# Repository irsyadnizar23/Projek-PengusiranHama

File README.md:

# Projek-Sistem Pengusiran hama otomatis berbasis mikrokontroler AVR 

Serangan hama dapat menyebabkan kerusakan yang signifikan pada tanaman dan menurunkan produktivitas. Untuk mengatasi masalah ini, saya mencoba mengembangkan sebuah sistem pengusiran hama otomatis berbasis mikrokontroler AVR. Sistem ini dirancang untuk mendeteksi keberadaan hama secara otomatis dan mengusir hama tersebut dengan metode yang efektif dan ramah lingkungan

---
Anggota
1. Rizal Fadhillah Muhammad (2122500032)
2. Samuel Windez Ambarita (2122500036)
3. Muhammad Irsyad Nizar Fazari (2122500050)
4. Nyoman Darma Saputra (2122500053)
5. Nashry Haliim Risantosa (2122500054)
---
## Komponen / alat yang diperlukan

1. Arduino Uno

   Mikrokontroler AVR bertindak sebagai otak dari sistem ini. Mikrokontroler akan menerima input dari sensor hama dan memproses data tersebut jika terdeteksi adanya       aktivitas hama

2. Led 3mm

   Sebagai indikator kepada para petani ketika hama datang menyerang 

3. Speaker

   Sebagai output suara dari hasil rekaman suara audacity kita  yang dapat didengar ketika kita menekan push button  

4. push Button(2)

   Push button kita menggunakan 2 push button yang push button pertama digunakan sebagai tombol untuk mengeluarkan suara hewan binatang buas dan push button kedua          digunakan sebagai suara ultrasonik dengan frekuensi tinggi 

5. Sensor sw 420

   sensor getaran yang digunakan untukMendeteksi keberadaan hama yang masuk di area pertanian dan mengirimkan sinyal ke mikrokontroler

6. PAM 8403

   Digunakan untuk menghasilkan output suara yang cukup keras dengan konsumsi daya yang rendah.

7. Pin Header male dan female

   sebagai soket tempat menghubungkan kabel-kabel konektor 

8. resistor 1k
9. Tip31c

---
## Skematik projek
Schematik

Board

Bottom

Top

LInk (https://youtu.be/SObbZaz81MM)
---
## Blog diagram

Cara Kerja

1. Saat ada Tikus atau Burung Pipit yang melewati atau menyentuh Padi Akan Membuat Padi Bergerak/bergetar
2. Getaran Dari Padi akan Di Deteksi Oleh Sensor Getar dan menghasilkan Sinyal Yang akan di kirim ke Mikrokontroler
3. Setelah Sinyal dari Sensor getar Di Terima oleh Mikrokontroler Maka Akan Membuat Led Menyala 
4. Dimana Disini LED sebagai Indikator terdapat Keberadaan Hama, Dimana Petani Dapat Menekan tombol (Button) seusai LED menyala yang akan Mengaktifkan Suara Pengusir Hama
5. Suara Output dari Mikrokontroler akan Di kuatkan Oleh Amplifier (penguat), Yang mana Suara Akan di keluarkan pada Speaker 
6. lalu Suara Yang akan di Keluarkan adalah Suara Hewan Buas contohnya Harimau, yang mana akan mengusir Tikus Dan Burung Pipit dari Tumbuhan Padi
---
## Simulasi projek
Disini kita coba mensimulasikan dengan menggunakan aplikasi wokwi

![Simulasi di wokwi] (https://wokwi.com/projects/398310246027706369)

LINK (https://youtu.be/nzQVdEaNT4E?si=r3UM6CYokPurmcue)
---
## Gambar Desain 3D
Tampak depan

Tampak samping

Dengan Dimensi

Tampak dalam

Hasil akhir 

Link Youtube
(https://youtu.be/AhoeIHWYmVM?si=7fZwOTttmSZrGxfX)

![Uploading 3d Desain] https://github.com/irsyadnizar23/Projek-PengusiranHama/blob/main/Desain%203D/File/alat%20pengusir%20hama%20new%20(1).blend

## Hasil cetak PCB

## Sistem audio
Disini untuk pembuatan audio kita menggunakan software audacity dan HXD yang kita gunakan untuk merekam hasil suara rekaman kita atau suara yang telah kita download bebrbentuk mp3
Berikut langkah langkah mengkonversi audio dari audacity hingga menjadi bahasa C:

   1. Buka aplikasi audacity
   2. Rekam suara atau dapat ambil audio dari web
   3. Setelah melakukan perekaman audio akan menghasilkan seperti dibawah ini

   4. Setelah diset noise nya agar pada audio tidak terdapat sebuah noise

   5. Export audio ke bentuk RAW

   6. Buka aplikasi HXD
   7. Klik open lalu pilih file RAW yang telah kita ekspor dari audacity

   8. lalu klik file lalu pilih export ke C, selanjutnya buka vs code pilih file yang telah kita export dari HXD

  LINK AUDACITY
  https://youtu.be/fRlAp86dA1M?si=hetPyFKCUFnrN079
  
## Dokumentasi Proses pengerjaan 
1. Mencoba sistem pada wokwi

2. Membuat desain 3d

3. Membuat shematik dan Board pada software eagle

4. pembelian komponen komponen yang diperlukan

5. Mensolder komponen pada PCB

6. Pembentukan casing menggunakan bor

7. Membuat rekaman audio pada audacity dan HXD

8. Membuat program pada arduino menggunakan arduino ide

9. Pengujian alat

Link simulasi 

(https://youtu.be/wmhCAvP-0ZI)

## Flyer

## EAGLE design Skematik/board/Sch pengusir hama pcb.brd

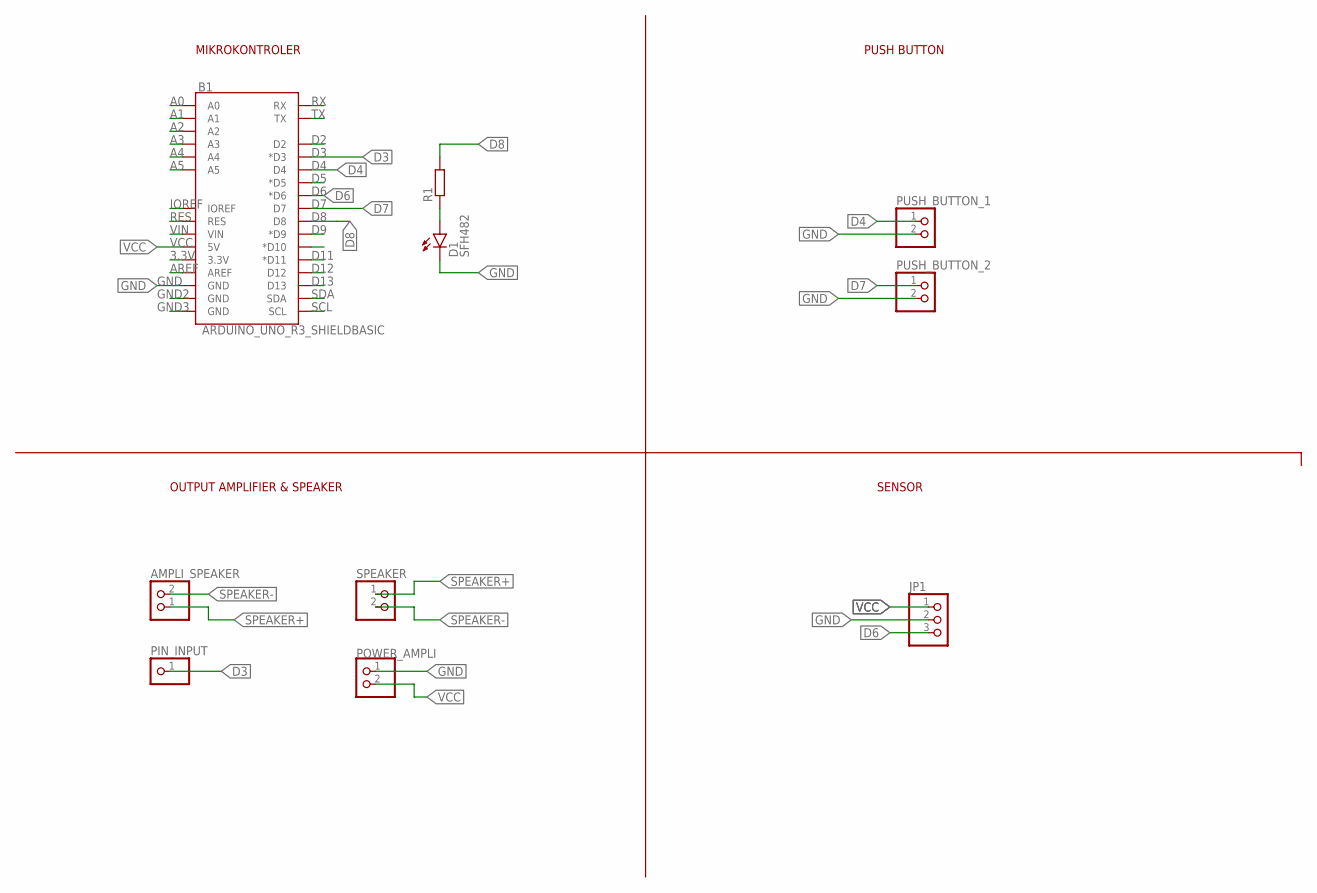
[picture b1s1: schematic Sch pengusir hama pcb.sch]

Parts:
AMPLI_SPEAKER: PINHD-1X2; 1X02
B1: ARDUINO_UNO_R3_SHIELDBASIC; UNO_R3_SHIELD
D1: SFH482
JP1: PINHD-1X3; 1X03
PIN_INPUT: PINHD-1X1; 1X01
POWER_AMPLI: PINHD-1X2; 1X02
PUSH_BUTTON_1, PUSH_BUTTON_2: PINHD-1X2; 1X02
R1: R-EU_0207/7; 0207/7
SPEAKER: PINHD-1X2; 1X02

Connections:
3.3V: B1.3.3V
A0: B1.A0
A1: B1.A1
A2: B1.A2
A3: B1.A3
A4: B1.A4
A5: B1.A5
AREF: B1.AREF
D2: B1.D2
D3: B1.D3 (*D3), PIN_INPUT.1
D4: B1.D4, PUSH_BUTTON_1.1
D5: B1.D5 (*D5)
D6: B1.D6 (*D6), JP1.3
D7: B1.D7, PUSH_BUTTON_2.1
D8: B1.D8, R1.2
D9: B1.D9 (*D9)
D10: B1.D10 (*D10)
D11: B1.D11 (*D11)
D12: B1.D12
D13: B1.D13
GND: B1.GND@2 (GND), D1.K (C), JP1.2, POWER_AMPLI.1, PUSH_BUTTON_1.2, PUSH_BUTTON_2.2
GND2: B1.GND@1 (GND)
GND3: B1.GND@0 (GND)
IOREF: B1.IOREF
unnamed: D1.A, R1.1
RES: B1.RES
RX: B1.RX
SCL: B1.SCL
SDA: B1.SDA
SPEAKER+: AMPLI_SPEAKER.1, SPEAKER.1
SPEAKER-: AMPLI_SPEAKER.2, SPEAKER.2
TX: B1.TX
VCC: B1.5V, JP1.1, POWER_AMPLI.2
VIN: B1.VIN

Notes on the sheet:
SENSOR
PUSH BUTTON
MIKROKONTROLER
OUTPUT AMPLIFIER & SPEAKER

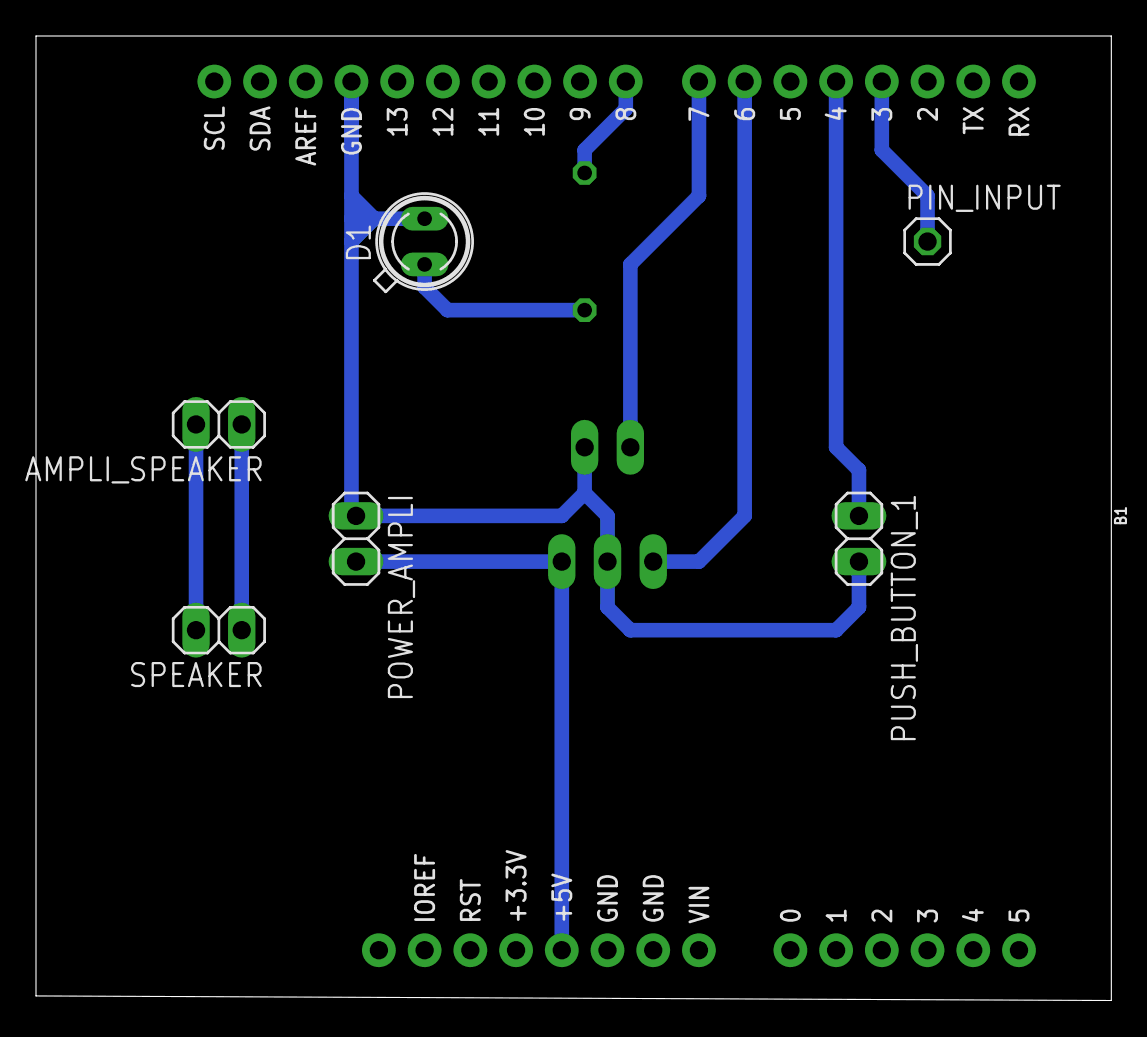
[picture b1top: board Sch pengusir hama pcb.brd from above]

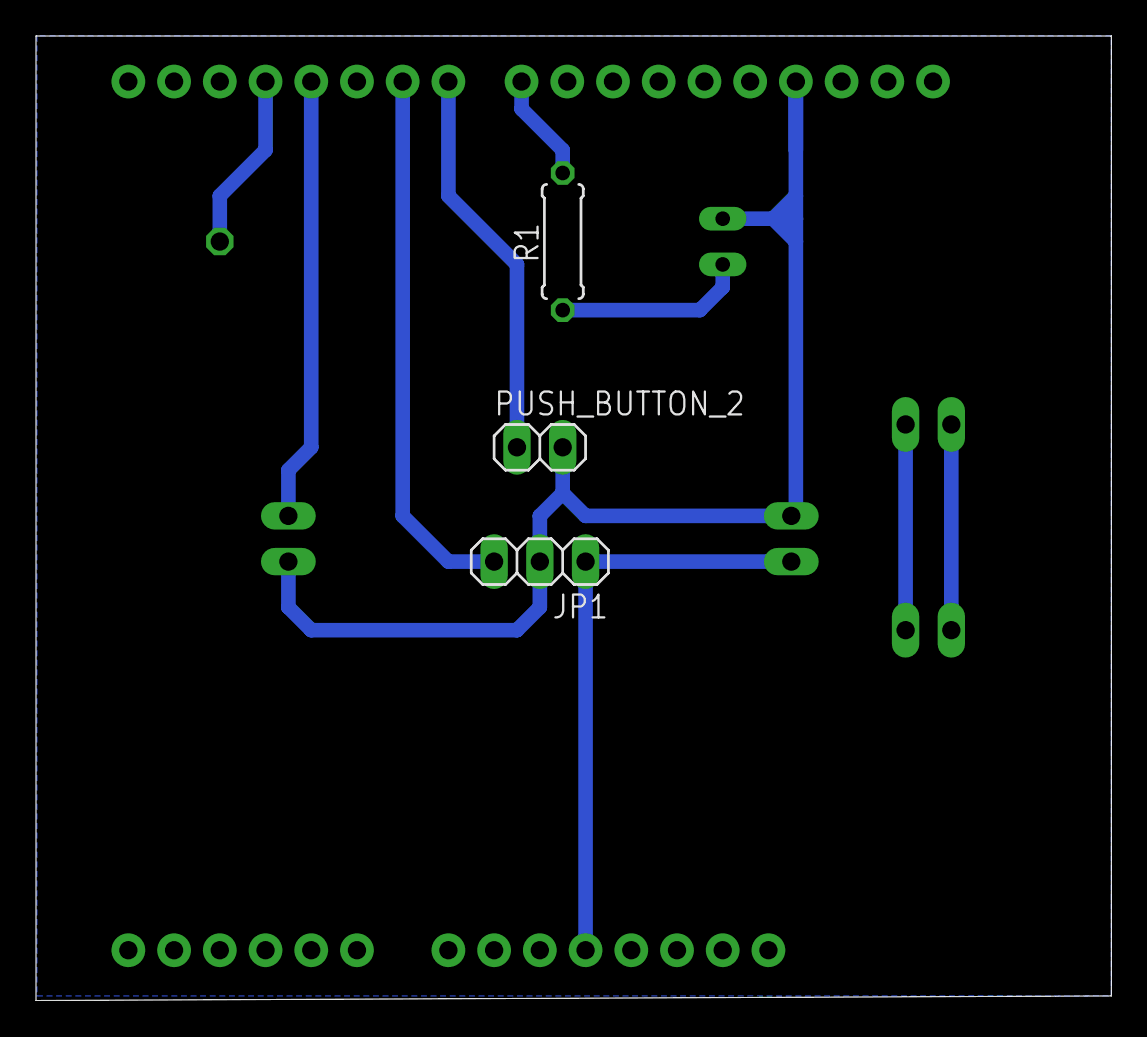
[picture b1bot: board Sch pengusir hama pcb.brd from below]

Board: 2 copper layers, 59.7 x 53.6 mm, 10 parts (3 on the bottom side), 10 nets.

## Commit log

2024-05-13 Pemutakhiran Blog Diagram Hama.drawio
2024-05-13 Blog Diagram Hama.drawio.png ditambahkan
2024-05-14 Create Desain
2024-05-14 Create Skematik Projek
2024-05-14 Create Artikel Jurnla
2024-05-14 Create Blok diagram
2024-05-20 README.md
2024-05-20 Create foto
2024-05-20 Create program
2024-05-20 Create Hasil dari alat
2024-05-20 Create Hasil alat
2024-05-20 Create dokumentasi
2024-05-21 Update program
2024-05-27 Create board
2024-05-27 Create SCH
2024-06-02 Create p
2024-06-03 Create projek

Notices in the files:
parts and their libraries:
SparkFun-Boards: Licensing: Creative Commons ShareAlike 4.0 International - https://creativecommons.org/licenses/by-sa/4.0
